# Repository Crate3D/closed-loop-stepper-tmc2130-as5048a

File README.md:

# closed-loop-stepper-tmc2130-as5048a
Closed loop stepper using tmc2130 and as5048a

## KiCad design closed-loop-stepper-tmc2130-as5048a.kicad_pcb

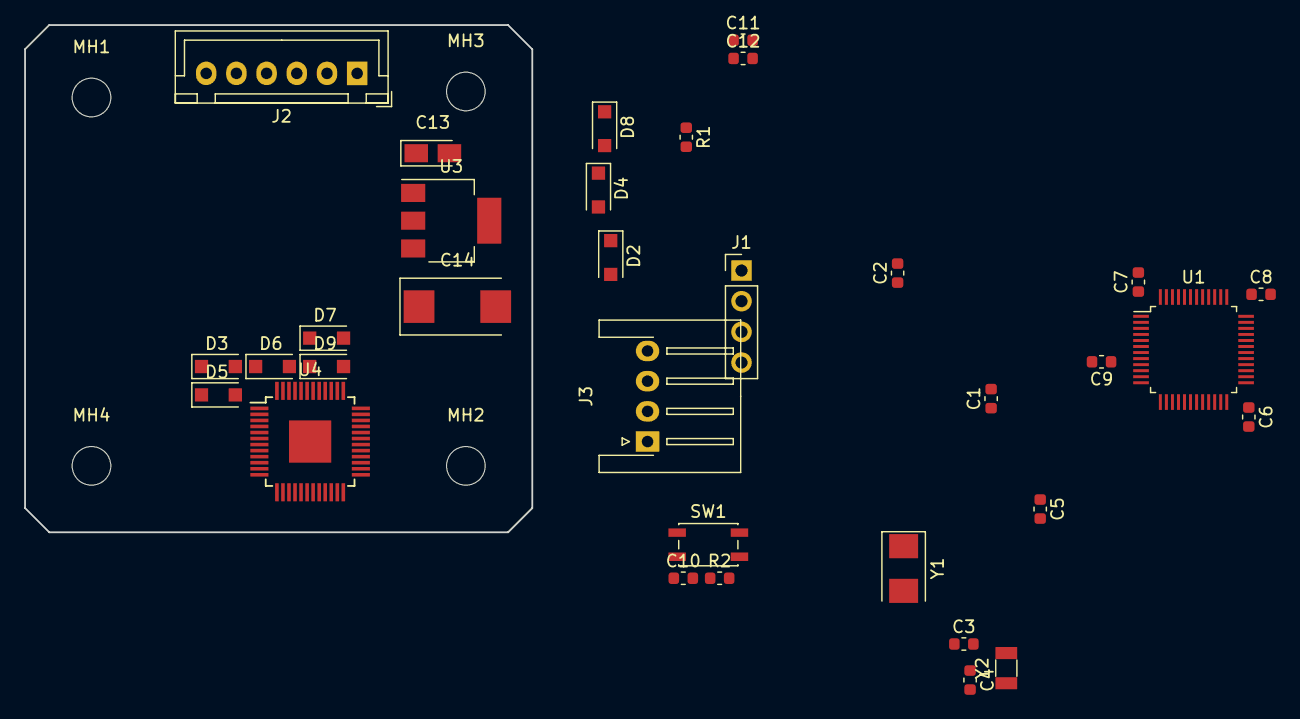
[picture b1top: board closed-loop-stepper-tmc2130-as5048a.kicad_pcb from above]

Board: 2 copper layers, 42.0 x 42.0 mm, 38 parts (1 on the bottom side), 14 nets, no tracks yet.

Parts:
C1, C2, C3, C4: 20pF; C_0603_1608Metric
C5, C6, C7, C8, C9, C11: 100nF; C_0603_1608Metric
C10: 1uF; C_0603_1608Metric
C12: 10uF; C_0603_1608Metric
C13: 0.47uF; CP_Tantalum_Case-A_EIA-3216-18_Reflow
C14: 22uF; CP_Tantalum_Case-X_EIA-7343-43_Reflow
D2, D3, D4, D5, D6, D7, D8, D9: S310FA; D_SOD-123F
J1: SWD; PinHeader_1x04_P2.54mm_Vertical
J2: Conn_01x06; JST_XH_B06B-XH-A_1x06_P2.50mm_Vertical
J3: Conn_01x04; JST_XH_S04B-XH-A-1_1x04_P2.50mm_Horizontal
MH1, MH2, MH3, MH4: MountingHole; MountingHole_3.2mm_M3
R1: 1M; R_0603_1608Metric
R2: 10K; R_0603_1608Metric
SW1: RESET; SW_SPST_EVQP2
U1: STM32F103C8T6; LQFP-48_7x7mm_P0.5mm
U2: AS5048A; TSSOP-14_4.4x5mm_P0.65mm
U3: TS2940CW 33 RPG; SOT-223-3_TabPin2
U4: TMC2130-TA; TQFP-48-1EP_7x7mm_P0.5mm_EP3.5x3.5mm
Y1: 8M; Crystal_SMD_5032-2Pin_5.0x3.2mm
Y2: 32.768K; Crystal_SMD_3215-2Pin_3.2x1.5mm

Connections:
+3V3: C5.1, C6.1, C7.1, C8.1, C9.1, C11.2, C12.2, C14.1, J1.4, R2.1, U1.9, U1.24, U1.36, U1.48, U3.3
GND: C1.1, C2.2, C3.2, C4.2, C5.2, C6.2, C7.2, C8.2, C9.2, C10.2, C11.1, C12.1, C13.2, C14.2, D3.2, D5.2, D7.2, D9.2, J1.1, J2.2, SW1.1, U1.8, U1.23, U1.35, U1.47, U3.2
OA1: D8.2, D9.1, J3.1, U4.46
OA2: D6.2, D7.1, J3.2, U4.42
OB1: D4.2, D5.1, J3.3, U4.15
OB2: D2.2, D3.1, J3.4, U4.19
OSCIN: C1.2, R1.1, U1.5, Y1.1
OSCOUT: C2.1, R1.2, U1.6, Y1.2
PC14: C3.1, U1.3, Y2.1
PC15: C4.1, U1.4, Y2.2
RESET: C10.1, R2.2, SW1.2, U1.7
SWDCLK: J1.2, U1.37
SWDIO: J1.3, U1.34
VCC: C13.1, D2.1, D4.1, D6.1, D8.1, J2.1, U3.1

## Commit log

2018-12-14 Unfinished board
2018-12-22 Fix project library path
    Fix TMC2130.lib path in sym-lib-table for project
2019-01-30 Replace power subsystem
